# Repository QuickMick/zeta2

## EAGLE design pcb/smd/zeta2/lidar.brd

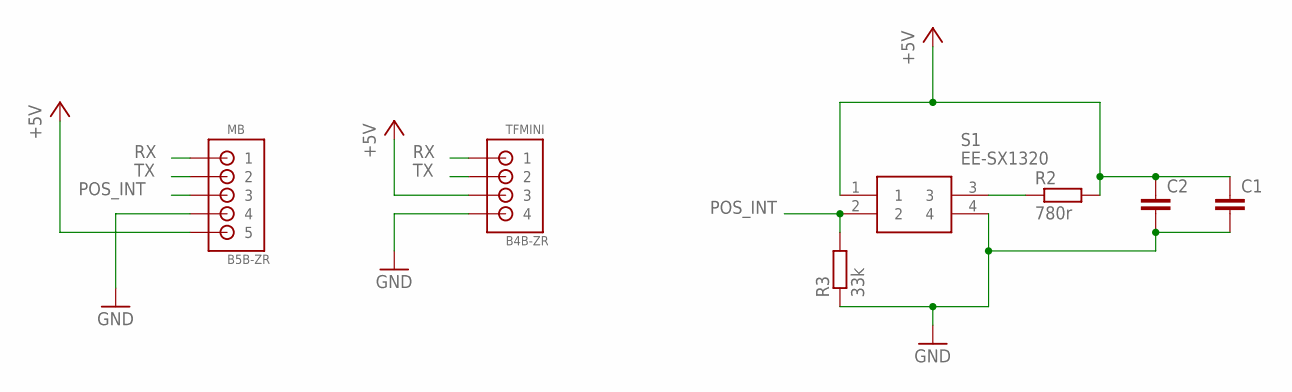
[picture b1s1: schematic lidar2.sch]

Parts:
C1: C-EUC1206; C1206
C2: C-EUC0805; C0805
MB: B5B-ZR
R2: 780r; R0603
R3: 33k; R0603
S1: EE-SX1320
TFMINI: B4B-ZR

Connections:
+5V: C1.1, C2.1, MB.5, R2.2, S1.1, TFMINI.3
GND: C1.2, C2.2, MB.4, R3.1, S1.4, TFMINI.4
unnamed: R2.1, S1.3
POS_INT: MB.3, R3.2, S1.2
RX: MB.1, TFMINI.1
TX: MB.2, TFMINI.2

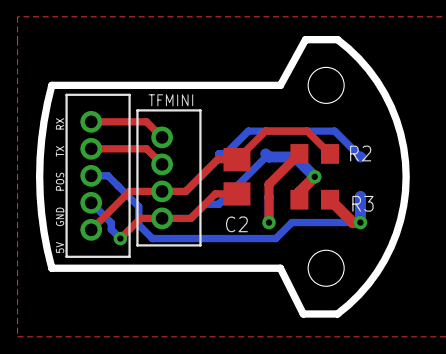
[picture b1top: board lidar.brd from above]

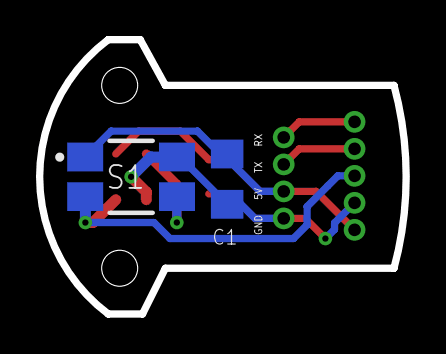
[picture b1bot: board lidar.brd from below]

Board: 2 copper layers, 20.4 x 15.2 mm, 7 parts (2 on the bottom side), 6 nets.

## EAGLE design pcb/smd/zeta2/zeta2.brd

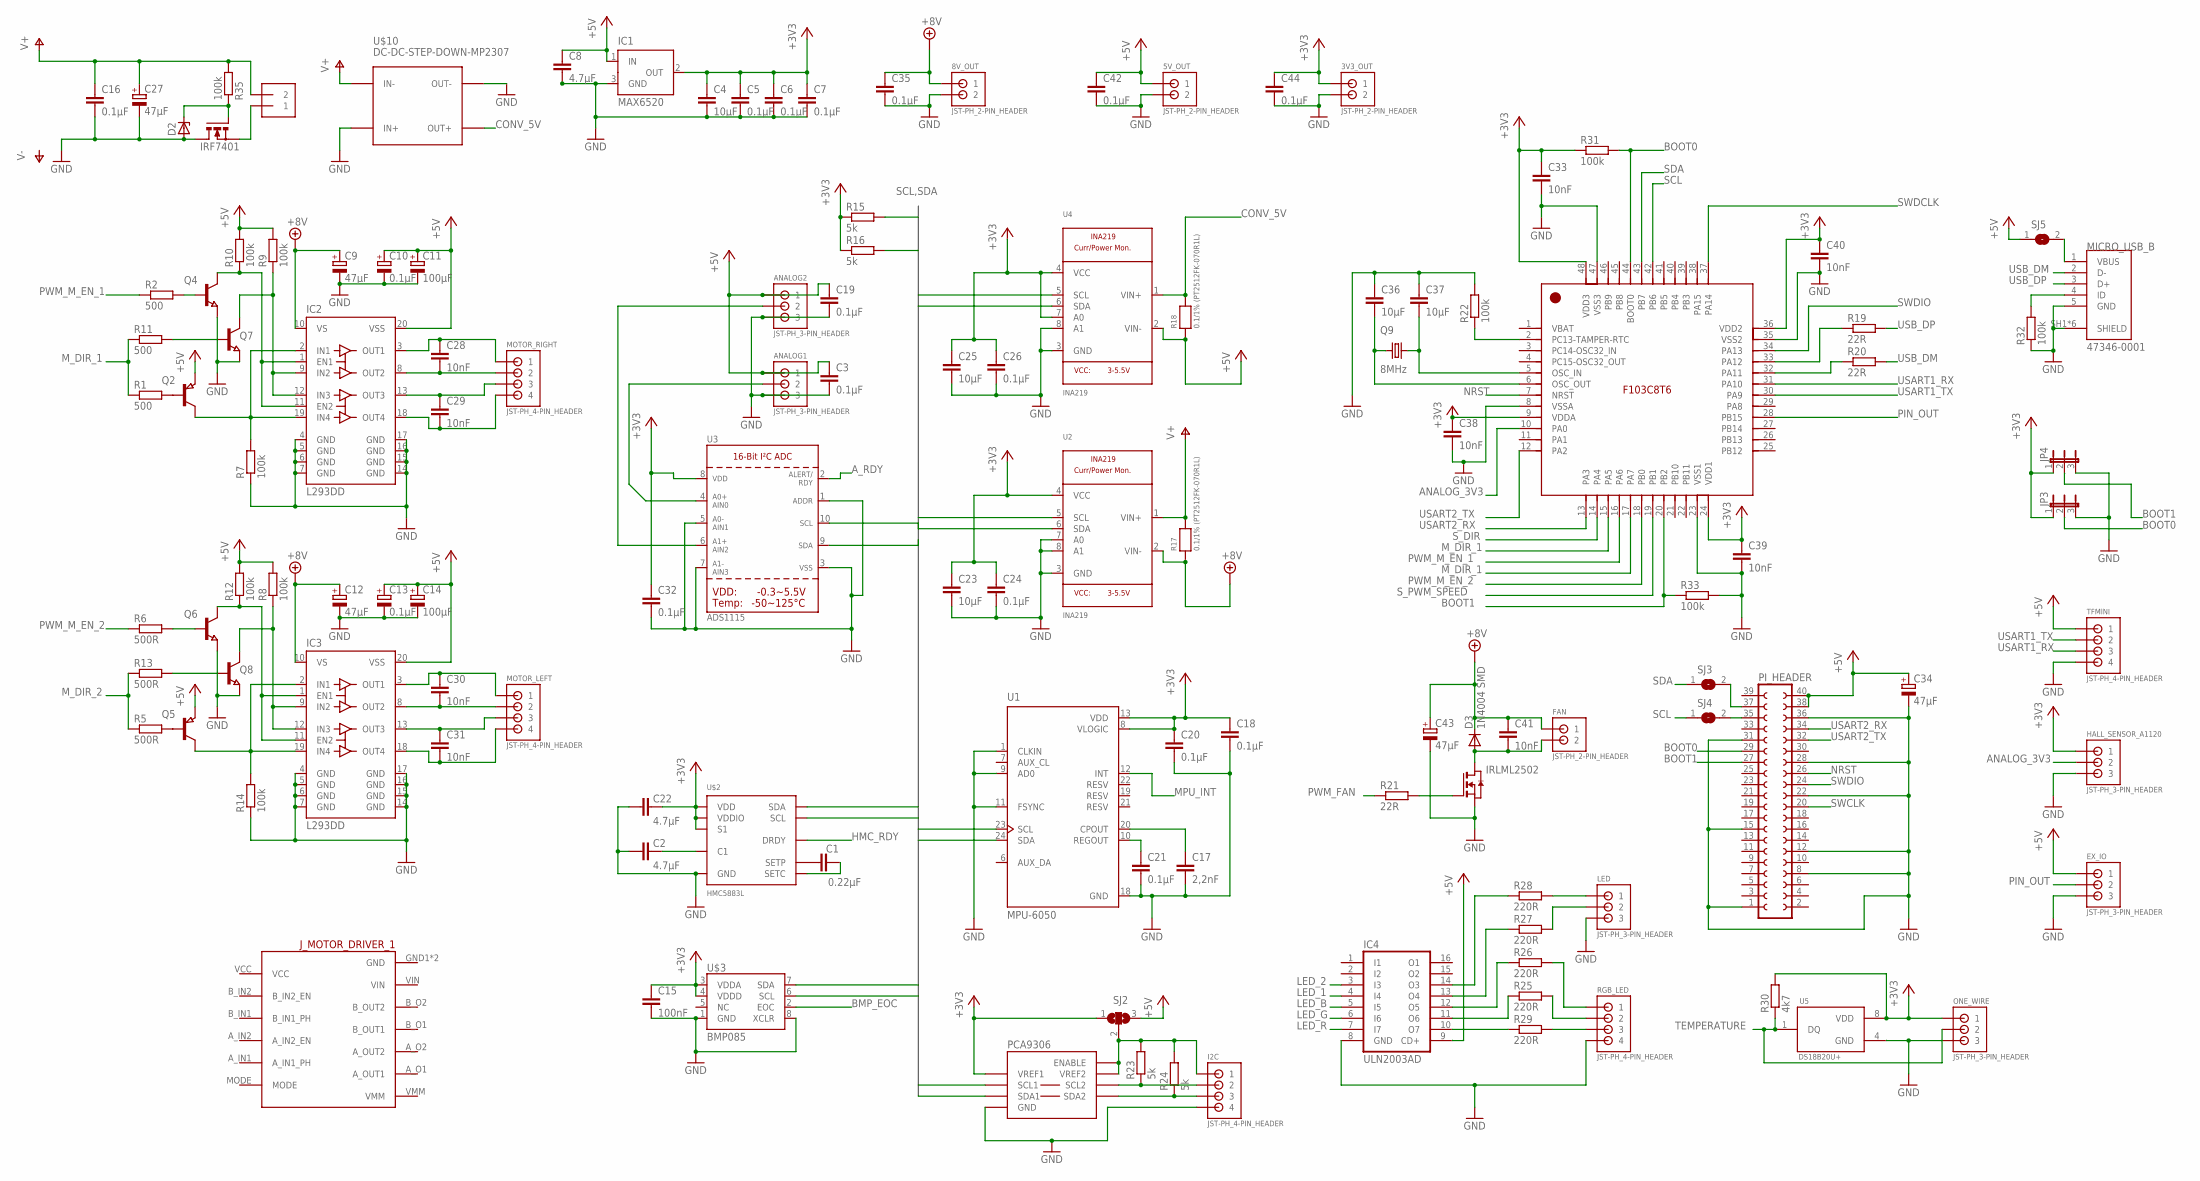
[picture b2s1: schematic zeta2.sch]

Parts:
3V3_OUT, 5V_OUT, 8V_OUT: JST-PH_2-PIN_HEADER; JST_B2B-PH_HEADER
ANALOG1, ANALOG2: JST-PH_3-PIN_HEADER; JST_B3B-PH_HEADER
C1: 0.22µF; C0603
C2, C8, C22: 4.7µF; C0603
C3, C5, C6, C7, C16, C18, C19, C20, C21, C24, C26, C32, C35, C42, C44: 0.1µF; C0603
C4, C23, C25, C36, C37: 10µF; C0603
C9, C12, C27, C34, C43: 47µF; SMC_C
C10, C13: 0.1µF; SMC_A
C11, C14: 100µF; SMC_C
C15: 100nF; C0603
C17: 2,2nF; C0603
C28, C29, C30, C31, C33, C38, C39, C40, C41: 10nF; C0603
D2: ZENER-DIODESOD80C; SOD80C
D3: 1N4004 SMD; MELF-MLL41
EX_IO: JST-PH_3-PIN_HEADER; JST_B3B-PH_HEADER
FAN: JST-PH_2-PIN_HEADER; JST_B2B-PH_HEADER
HALL_SENSOR_A1120: JST-PH_3-PIN_HEADER; JST_B3B-PH_HEADER
I2C: JST-PH_4-PIN_HEADER; JST_B4B-PH_HEADER
IC1: MAX6520; SOT23
IC2, IC3: L293DD; SO20
IC4: ULN2003AD; SO16
IRF7401: N-MOSFET-SO8S; SO-08
IRLML2502: NMOSSOT23; SOT-23
JP3, JP4: JP2E; JP2
J_MOTOR_DRIVER_1: MOTOR_DRIVER; MOTOR_DRIVER_FOOTPRINT
LED: JST-PH_3-PIN_HEADER; JST_B3B-PH_HEADER
MICRO_USB_B: 47346-0001; MOLEX_47346-0001
MOTOR_LEFT: JST-PH_4-PIN_HEADER; JST_B4B-PH_HEADER
MOTOR_RIGHT: JST-PH_4-PIN_HEADER; JST_B4B-PH_HEADER
ONE_WIRE: JST-PH_3-PIN_HEADER; JST_B3B-PH_HEADER
PCA9306: IC2_LEVEL_TRANSLATER; SOIC-8
PI_HEADER: FE20-2
Q2, Q5: PNP-TRANSISTOR_SOT23; SOT23
Q4, Q6, Q7, Q8: NPN-TRANSISTOR_SOT23; SOT23
Q9: 8MHz; 7.0X5.0
R1, R2, R11: 500; R0603
R5, R6, R13: 500R; R0603
R7, R8, R9, R10, R12, R14, R22, R31, R32, R33, R35: 100k; R0603
R15, R16, R23, R24: 5k; R0603
R17, R18: 0.1/1% (PT2512FK-070R1L); 2512
R19, R20, R21: 22R; R0603
R25, R26, R27, R28, R29: 220R; R0603
R30: 4k7; R0603
RGB_LED: JST-PH_4-PIN_HEADER; JST_B4B-PH_HEADER
SJ2: SJ2W; SJ_2
SJ3, SJ4, SJ5: SOLDERJUMPERREFLOW_NOPASTE; SOLDERJUMPER_REFLOW_NOPASTE
SUPPLY_IN: TERMBLOCK_1X2-3.5MM; 1X2-3.5MM
TFMINI: JST-PH_4-PIN_HEADER; JST_B4B-PH_HEADER
U1: MPU-6050; QFN50P400X400X95-24N
U2, U4: INA219; SOT23-8
U3: ADS1115; MSOP10
U5: DS18B20U+; SOP65P490X95-8N
U$1: STM32F103C8T6; LQFP48_7X7MM_0.5MMPP
U$2: HMC5883L; LPCC-16
U$3: BMP085
U$10: DC-DC-STEP-DOWN-MP2307

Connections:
+3V3: 3V3_OUT.P1 (1), C4.1, C5.1, C6.1, C7.1, C15.1, C18.1, C20.1, C22.1, C23.1, C24.1, C25.1, C26.1, C32.1, C33.1, C38.1, C39.1, C40.1, C44.1, HALL_SENSOR_A1120.P1 (1), IC1.2 (OUT), JP3.1, JP4.1, ONE_WIRE.P1 (1), PCA9306.1 (VREF1), R15.1, R16.1, R30.2, R31.1, SJ2.1, U1.8 (VLOGIC), U1.13 (VDD), U2.4 (VCC), U3.8 (VDD), U4.4 (VCC), U4.7 (A0), U5.8 (VDD), U$1.9 (VDDA), U$1.24 (VDD1), U$1.36 (VDD2), U$1.48 (VDD3), U$2.2 (VDD), U$2.4 (S1), U$2.13 (VDDIO), U$3.3 (VDDA), U$3.4 (VDDD)
+5V: 5V_OUT.P1 (1), ANALOG1.P1 (1), ANALOG2.P1 (1), C3.1, C8.1, C10.+, C11.+, C13.+, C14.+, C19.1, C34.+, C42.1, EX_IO.P1 (1), IC1.1 (IN), IC2.20 (VSS), IC3.20 (VSS), IC4.9 (CD+), PI_HEADER.38, PI_HEADER.40, Q2.2 (E), Q5.2 (E), R8.2, R9.2, R10.2, R12.2, R18.1, SJ2.3, SJ5.1, TFMINI.P1 (1), U4.2 (VIN-)
+8V: 8V_OUT.P1 (1), C9.+, C12.+, C35.1, C41.1, C43.+, D3.C, FAN.P1 (1), IC2.10 (VS), IC3.10 (VS), R17.1, U2.2 (VIN-)
ANALOG_3V3: HALL_SENSOR_A1120.P2 (2), U$1.10 (PA0)
A_RDY: U3.2 (ALERT/RDY)
BMP_EOC: U$3.2 (EOC)
BOOT0: JP3.2, PI_HEADER.29, R31.2, U$1.44 (BOOT0)
BOOT1: JP4.2, PI_HEADER.27, R33.1, U$1.20 (PB2)
CONV_5V: R18.2, U4.1 (VIN+), U$10.OUT+
GND: 3V3_OUT.P2 (2), 5V_OUT.P2 (2), 8V_OUT.P2 (2), ANALOG1.P3 (3), ANALOG2.P3 (3), C2.2, C3.2, C4.2, C5.2, C6.2, C7.2, C8.2, C9.-, C10.-, C11.-, C12.-, C13.-, C14.-, C15.2, C16.2, C17.2, C18.2, C19.2, C20.2, C21.2, C22.2, C23.2, C24.2, C25.2, C26.2, C27.-, C32.2, C33.2, C34.-, C35.2, C36.1, C37.1, C38.2, C39.2, C40.2, C42.2, C43.-, C44.2, D2.A, EX_IO.P3 (3), HALL_SENSOR_A1120.P3 (3), I2C.P4 (4), IC1.3 (GND), IC2.4 (GND), IC2.5 (GND), IC2.6 (GND), IC2.7 (GND), IC2.14 (GND), IC2.15 (GND), IC2.16 (GND), IC2.17 (GND), IC3.4 (GND), IC3.5 (GND), IC3.6 (GND), IC3.7 (GND), IC3.14 (GND), IC3.15 (GND), IC3.16 (GND), IC3.17 (GND), IC4.8 (GND), IRF7401.5 (D), IRF7401.6 (D), IRF7401.7 (D), IRF7401.8 (D), IRLML2502.2 (S), JP3.3, JP4.3, LED.P3 (3), MICRO_USB_B.5 (GND), MICRO_USB_B.SH1 (SHIELD), MICRO_USB_B.SH2 (SHIELD), MICRO_USB_B.SH3 (SHIELD), MICRO_USB_B.SH4 (SHIELD), MICRO_USB_B.SH5 (SHIELD), MICRO_USB_B.SH6 (SHIELD), ONE_WIRE.P3 (3), PCA9306.4 (GND), PI_HEADER.1, PI_HEADER.8, PI_HEADER.12, PI_HEADER.15, PI_HEADER.22, PI_HEADER.28, PI_HEADER.31, PI_HEADER.36, Q4.2 (E), Q6.2 (E), Q7.2 (E), Q8.2 (E), R7.1, R14.1, R22.2, R32.1, R33.2, RGB_LED.P4 (4), TFMINI.P4 (4), U1.1 (CLKIN), U1.9 (AD0), U1.11 (FSYNC), U1.18 (GND), U2.3 (GND), U2.7 (A0), U2.8 (A1), U3.1 (ADDR), U3.3 (VSS), U3.5 (AIN1), U3.7 (AIN3), U4.3 (GND), U4.8 (A1), U5.4 (GND), U$1.8 (VSSA), U$1.23 (VSS1), U$1.35 (VSS2), U$1.47 (VSS3), U$2.9 (GND), U$2.11 (GND), U$3.1 (GND), U$3.8 (XCLR), U$10.IN+, U$10.OUT-
HMC_RDY: U$2.15 (DRDY)
LED_1: IC4.4 (I4)
LED_2: IC4.3 (I3)
LED_B: IC4.5 (I5)
LED_G: IC4.6 (I6)
LED_R: IC4.7 (I7)
MPU_INT: U1.12 (INT)
M_DIR_1: R1.1, R11.1, U$1.15 (PA5), U$1.17 (PA7)
M_DIR_2: R5.1, R13.1
unnamed: IC2.9 (IN2), IC2.12 (IN3), Q7.3 (C), R9.1
unnamed: C1.2, U$2.12 (SETC)
unnamed: C1.1, U$2.8 (SETP)
unnamed: C2.1, U$2.10 (C1)
unnamed: IC2.2 (IN1), IC2.19 (IN4), Q2.3 (C), R7.2
unnamed: IC3.9 (IN2), IC3.12 (IN3), Q8.3 (C), R8.1
unnamed: IC3.2 (IN1), IC3.19 (IN4), Q5.3 (C), R14.2
unnamed: IC2.1 (EN1), IC2.11 (EN2), Q4.3 (C), R10.1
unnamed: IC3.1 (EN1), IC3.11 (EN2), Q6.3 (C), R12.1
unnamed: Q2.1 (B), R1.2
unnamed: Q7.1 (B), R11.2
unnamed: Q4.1 (B), R2.2
unnamed: Q5.1 (B), R5.2
unnamed: Q6.1 (B), R6.2
unnamed: Q8.1 (B), R13.2
unnamed: C17.1, U1.20 (CPOUT)
unnamed: C29.1, IC2.13 (OUT3), MOTOR_RIGHT.P3 (3)
unnamed: C29.2, IC2.18 (OUT4), MOTOR_RIGHT.P4 (4)
unnamed: C21.1, U1.10 (REGOUT)
unnamed: C28.2, IC2.8 (OUT2), MOTOR_RIGHT.P2 (2)
unnamed: C28.1, IC2.3 (OUT1), MOTOR_RIGHT.P1 (1)
unnamed: C31.1, IC3.13 (OUT3), MOTOR_LEFT.P3 (3)
unnamed: C31.2, IC3.18 (OUT4), MOTOR_LEFT.P4 (4)
unnamed: C30.2, IC3.8 (OUT2), MOTOR_LEFT.P2 (2)
unnamed: C30.1, IC3.3 (OUT1), MOTOR_LEFT.P1 (1)
unnamed: IC4.10 (O7), R29.1
unnamed: C36.2, Q9.1, U$1.6 (OSC_OUT)
unnamed: C37.2, Q9.3 (2), U$1.5 (OSC_IN)
unnamed: IRLML2502.3 (G), R21.2
unnamed: IC4.11 (O6), R25.1
unnamed: R20.1, U$1.32 (PA11)
unnamed: R19.1, U$1.33 (PA12)
unnamed: R22.1, U$1.2 (PC13-TAMPER-RTC)
unnamed: PI_HEADER.37, SJ3.2
unnamed: PI_HEADER.35, SJ4.2
unnamed: IC4.12 (O5), R26.1
unnamed: I2C.P1 (1), PCA9306.7 (VREF2), PCA9306.8 (ENABLE), R23.2, R24.2, SJ2.2
unnamed: I2C.P2 (2), PCA9306.6 (SCL2), R23.1
unnamed: I2C.P3 (3), PCA9306.5 (SDA2), R24.1
unnamed: IC4.13 (O4), R27.1
unnamed: IC4.14 (O3), R28.1
unnamed: MICRO_USB_B.4 (ID), R32.2
unnamed: LED.P1 (1), R28.2
unnamed: R29.2, RGB_LED.P3 (3)
unnamed: R25.2, RGB_LED.P2 (2)
unnamed: R26.2, RGB_LED.P1 (1)
unnamed: LED.P2 (2), R27.2
unnamed: MICRO_USB_B.1 (VBUS), SJ5.2
unnamed: ANALOG1.P2 (2), U3.4 (AIN0)
unnamed: ANALOG2.P2 (2), U3.6 (AIN2)
unnamed: C41.2, D3.A, FAN.P2 (2), IRLML2502.1 (D)
unnamed: D2.C, IRF7401.4 (G), R35.1
unnamed: IRF7401.1 (S), IRF7401.2 (S), IRF7401.3 (S), SUPPLY_IN.1
NRST: PI_HEADER.26, U$1.7 (NRST)
PIN_OUT: EX_IO.P2 (2), U$1.28 (PB15)
PWM_FAN: R21.1
PWM_M_EN_1: R2.1, U$1.16 (PA6)
PWM_M_EN_2: R6.1, U$1.18 (PB0)
SCL: PCA9306.2 (SCL1), R15.2, SJ4.1, U1.23 (SCL), U2.5 (SCL), U3.10 (SCL), U4.5 (SCL), U$1.42 (PB6), U$2.1 (SCL), U$3.6 (SCL)
SDA: PCA9306.3 (SDA1), R16.2, SJ3.1, U1.24 (SDA), U2.6 (SDA), U3.9 (SDA), U4.6 (SDA), U$1.43 (PB7), U$2.16 (SDA), U$3.7 (SDA)
SWCLK: PI_HEADER.20
SWDCLK: U$1.37 (PA14)
SWDIO: PI_HEADER.24, U$1.34 (PA13)
S_DIR: U$1.14 (PA4)
S_PWM_SPEED: U$1.19 (PB1)
TEMPERATURE: ONE_WIRE.P2 (2), R30.1, U5.1 (DQ)
USART1_RX: TFMINI.P3 (3), U$1.31 (PA10)
USART1_TX: TFMINI.P2 (2), U$1.30 (PA9)
USART2_RX: PI_HEADER.34, U$1.13 (PA3)
USART2_TX: PI_HEADER.32, U$1.12 (PA2)
USB_DM: MICRO_USB_B.2 (D-), R20.2
USB_DP: MICRO_USB_B.3 (D+), R19.2
V+: C16.1, C27.+, R17.2, R35.2, SUPPLY_IN.2, U2.1 (VIN+), U$10.IN-

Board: 2 copper layers, 126 parts (16 on the bottom side), 78 nets, no tracks yet.

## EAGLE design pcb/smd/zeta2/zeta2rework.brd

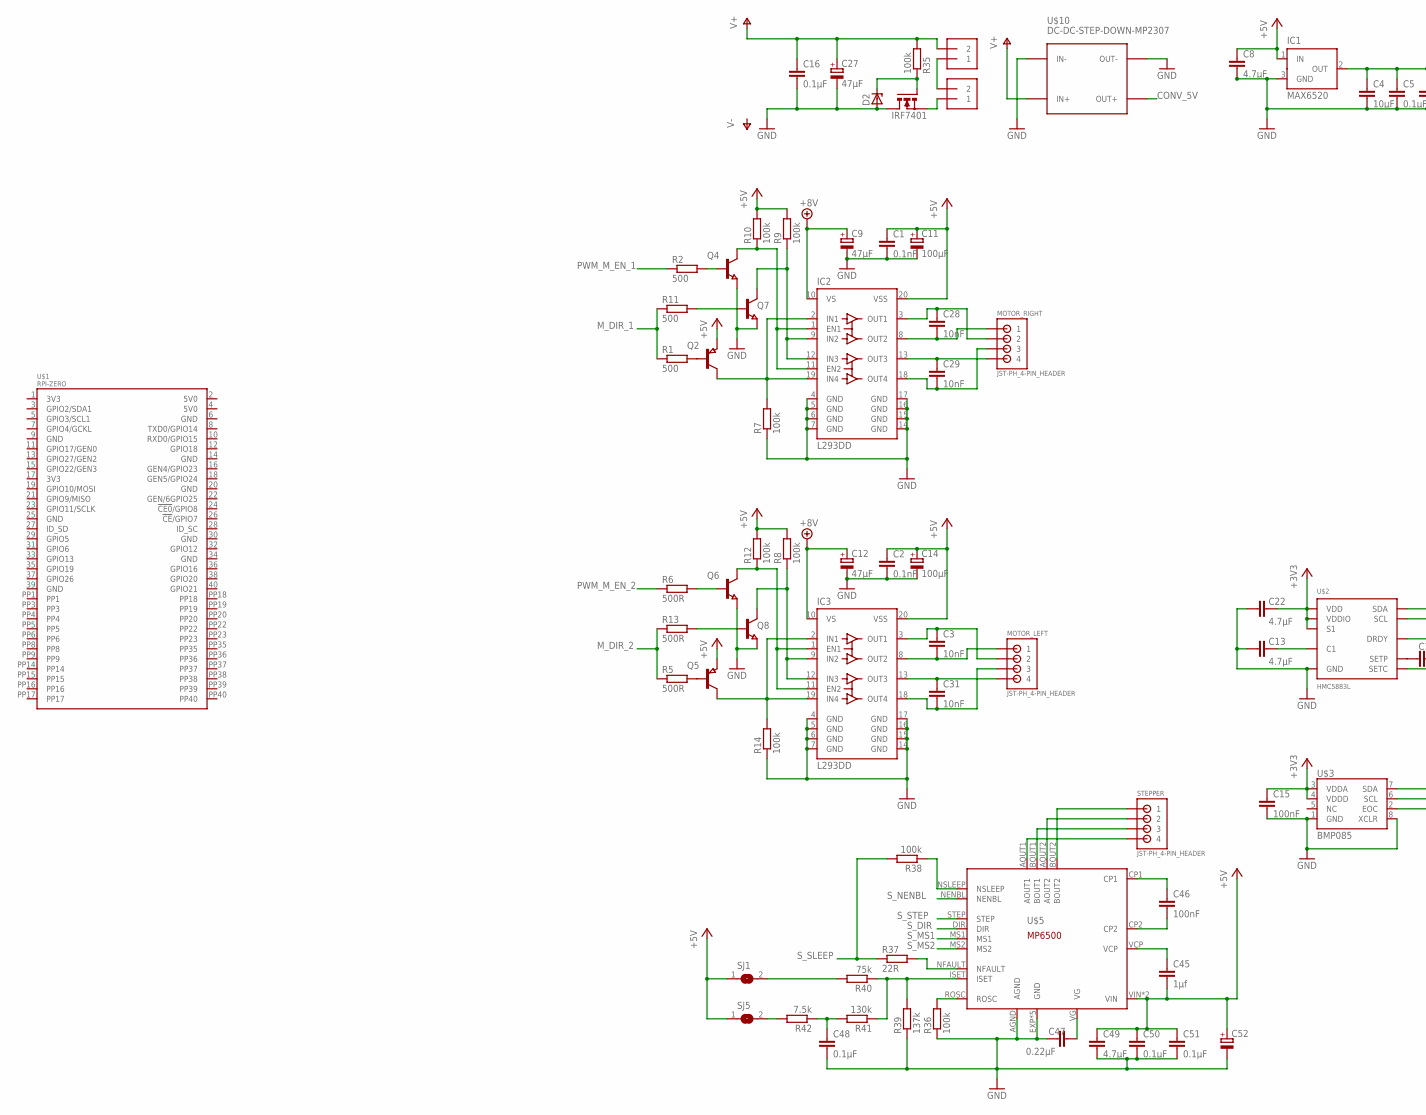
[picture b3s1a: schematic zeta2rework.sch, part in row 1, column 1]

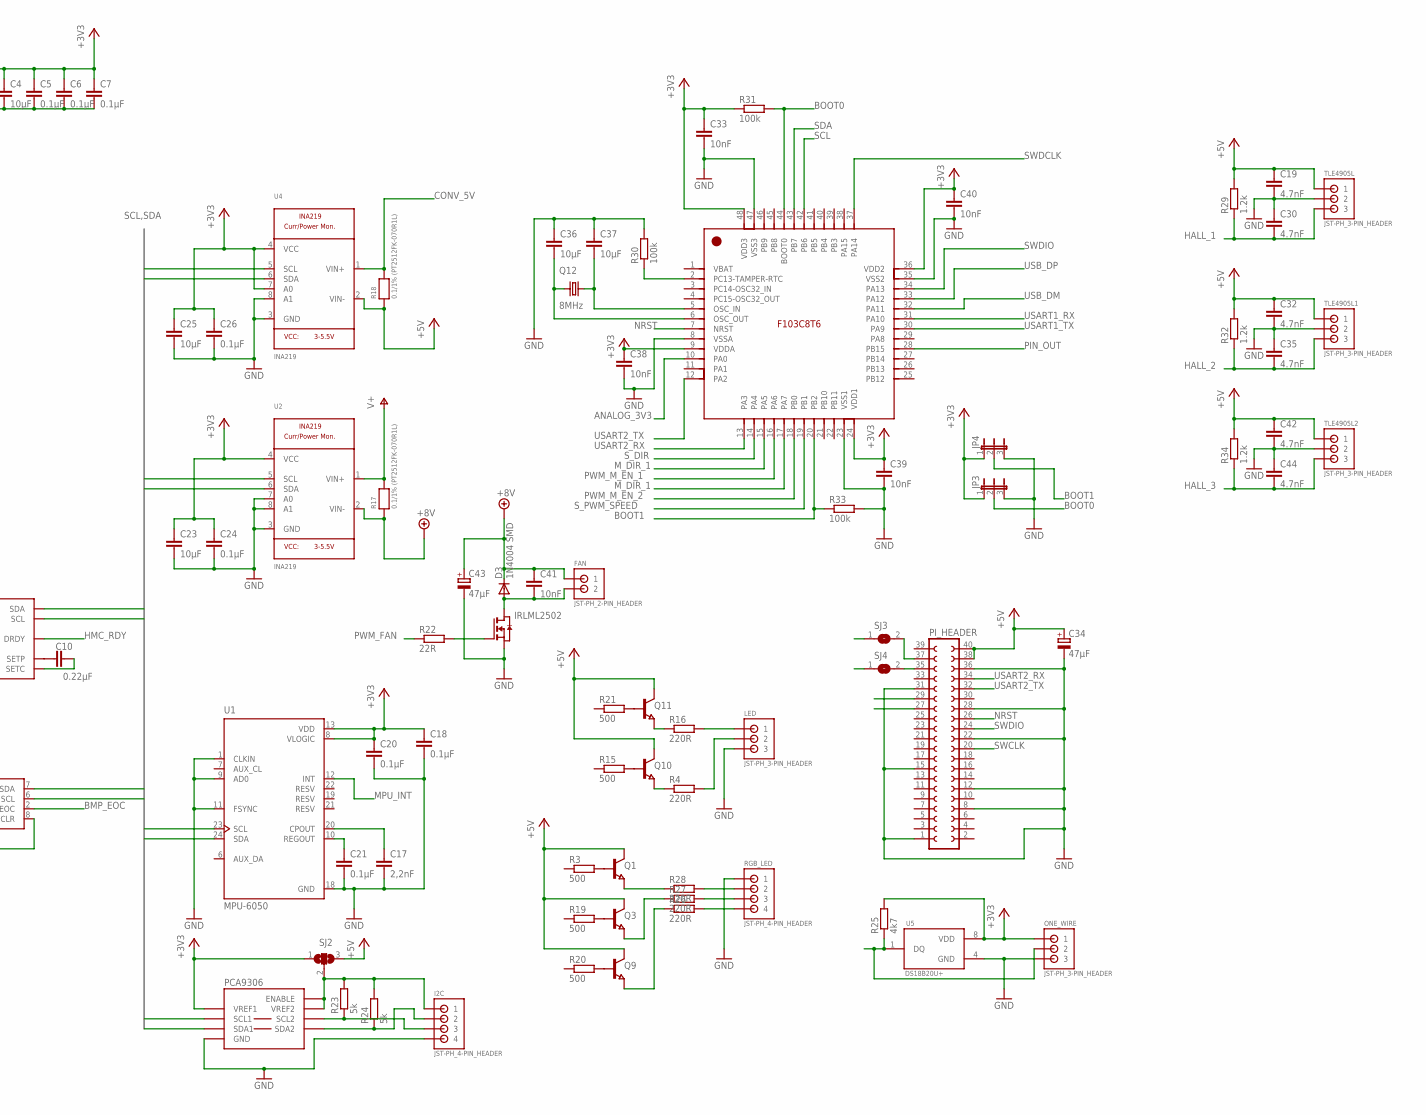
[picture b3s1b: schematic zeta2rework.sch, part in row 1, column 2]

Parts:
C1, C2: 0.1nF; C0603
C3, C28, C29, C31, C33, C38, C39, C40, C41: 10nF; C0603
C4, C23, C25, C36, C37: 10µF; C0603
C5, C6, C7, C16, C18, C20, C21, C24, C26, C48, C50, C51: 0.1µF; C0603
C8, C13, C22, C49: 4.7µF; C0603
C9, C12, C27, C34, C43: 47µF; SMC_C
C10, C47: 0.22µF; C0603
C11, C14: 100µF; SMC_C
C15, C46: 100nF; C0603
C17: 2,2nF; C0603
C19, C30, C32, C35, C42, C44: 4.7nF; C0603
C45: 1µf; C0603
C52: CPOL-EU150CLZ-0810; 150CLZ-0810
D2: ZENER-DIODESOD80C; SOD80C
D3: 1N4004 SMD; MELF-MLL41
FAN: JST-PH_2-PIN_HEADER; JST_B2B-PH_HEADER
I2C: JST-PH_4-PIN_HEADER; JST_B4B-PH_HEADER
IC1: MAX6520; SOT23
IC2, IC3: L293DD; SO20
IRF7401: N-MOSFET-SO8S; SO-08
IRLML2502: NMOSSOT23; SOT-23
JP3, JP4: JP2E; JP2
LED: JST-PH_3-PIN_HEADER; JST_B3B-PH_HEADER
MOTOR_LEFT: JST-PH_4-PIN_HEADER; JST_B4B-PH_HEADER
MOTOR_RIGHT: JST-PH_4-PIN_HEADER; JST_B4B-PH_HEADER
ONE_WIRE: JST-PH_3-PIN_HEADER; JST_B3B-PH_HEADER
PCA9306: IC2_LEVEL_TRANSLATER; SOIC-8
PI_HEADER: FE20-2
Q1, Q3, Q4, Q6, Q7, Q8, Q9, Q10, Q11: NPN-TRANSISTOR_SOT23; SOT23
Q2, Q5: PNP-TRANSISTOR_SOT23; SOT23
Q12: 8MHz; 7.0X5.0
R1, R2, R3, R11, R15, R19, R20, R21: 500; R0603
R4, R16, R26, R27, R28: 220R; R0603
R5, R6, R13: 500R; R0603
R7, R8, R9, R10, R12, R14, R30, R31, R33, R35, R36, R38: 100k; R0603
R17, R18: 0.1/1% (PT2512FK-070R1L); 2512
R22, R37: 22R; R0603
R23, R24: 5k; R0603
R25: 4k7; R0603
R29, R32, R34: 1.2k; R0603
R39: 137k; R0603
R40: 75k; R0603
R41: 130k; R0603
R42: 7.5k; R0603
RGB_LED: JST-PH_4-PIN_HEADER; JST_B4B-PH_HEADER
SJ1, SJ3, SJ4, SJ5: SOLDERJUMPERREFLOW_NOPASTE; SOLDERJUMPER_REFLOW_NOPASTE
SJ2: SJ2W; SJ_2
STEPPER: JST-PH_4-PIN_HEADER; JST_B4B-PH_HEADER
SUPPLY_IN, SUPPLY_IN1: TERMBLOCK_1X2-3.5MM; 1X2-3.5MM
TLE4905L, TLE4905L1, TLE4905L2: JST-PH_3-PIN_HEADER; JST_B3B-PH_HEADER
U1: MPU-6050; QFN50P400X400X95-24N
U2, U4: INA219; SOT23-8
U5: DS18B20U+; SOP65P490X95-8N
U$1: RPI-ZERO; RASP_PI_ZERO_BOARD_FULL
U$2: HMC5883L; LPCC-16
U$3: BMP085
U$4: STM32F103C8T6; LQFP48_7X7MM_0.5MMPP
U$5: MP6500; QFN24
U$10: DC-DC-STEP-DOWN-MP2307

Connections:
+3V3: C4.1, C5.1, C6.1, C7.1, C15.1, C18.1, C20.1, C22.1, C23.1, C24.1, C25.1, C26.1, C33.1, C38.1, C39.1, C40.1, IC1.2 (OUT), JP3.1, JP4.1, ONE_WIRE.P1 (1), PCA9306.1 (VREF1), R25.2, R31.1, SJ2.1, U1.8 (VLOGIC), U1.13 (VDD), U2.4 (VCC), U4.4 (VCC), U4.7 (A0), U5.8 (VDD), U$2.2 (VDD), U$2.4 (S1), U$2.13 (VDDIO), U$3.3 (VDDA), U$3.4 (VDDD), U$4.9 (VDDA), U$4.24 (VDD1), U$4.36 (VDD2), U$4.48 (VDD3)
+5V: C1.1, C2.1, C8.1, C11.+, C14.+, C19.1, C32.1, C34.+, C42.1, C45.2, C49.1, C50.1, C51.1, C52.+, IC1.1 (IN), IC2.20 (VSS), IC3.20 (VSS), PI_HEADER.38, PI_HEADER.40, Q1.3 (C), Q2.2 (E), Q3.3 (C), Q5.2 (E), Q9.3 (C), Q10.3 (C), Q11.3 (C), R8.2, R9.2, R10.2, R12.2, R18.1, R29.2, R32.2, R34.2, SJ1.1, SJ2.3, SJ5.1, TLE4905L.P1 (1), TLE4905L1.P1 (1), TLE4905L2.P1 (1), U4.2 (VIN-), U$5.VIN, U$5.VIN@1 (VIN)
+8V: C9.+, C12.+, C41.1, C43.+, D3.C, FAN.P1 (1), IC2.10 (VS), IC3.10 (VS), R17.1, U2.2 (VIN-)
ANALOG_3V3: U$4.10 (PA0)
BMP_EOC: U$3.2 (EOC)
BOOT0: JP3.2, R31.2, U$4.44 (BOOT0)
BOOT1: JP4.2, R33.1, U$4.20 (PB2)
BOOT2: PI_HEADER.29
BOOT3: PI_HEADER.27
CONV_5V: R18.2, U4.1 (VIN+), U$10.OUT+
GND: C1.2, C2.2, C4.2, C5.2, C6.2, C7.2, C8.2, C9.-, C11.-, C12.-, C13.2, C14.-, C15.2, C16.2, C17.2, C18.2, C19.2, C20.2, C21.2, C22.2, C23.2, C24.2, C25.2, C26.2, C27.-, C30.1, C32.2, C33.2, C34.-, C35.1, C36.1, C37.1, C38.2, C39.2, C40.2, C42.2, C43.-, C44.1, C47.1, C48.2, C49.2, C50.2, C51.2, C52.-, D2.A, I2C.P4 (4), IC1.3 (GND), IC2.4 (GND), IC2.5 (GND), IC2.6 (GND), IC2.7 (GND), IC2.14 (GND), IC2.15 (GND), IC2.16 (GND), IC2.17 (GND), IC3.4 (GND), IC3.5 (GND), IC3.6 (GND), IC3.7 (GND), IC3.14 (GND), IC3.15 (GND), IC3.16 (GND), IC3.17 (GND), IRF7401.5 (D), IRF7401.6 (D), IRF7401.7 (D), IRF7401.8 (D), IRLML2502.2 (S), JP3.3, JP4.3, LED.P3 (3), ONE_WIRE.P3 (3), PCA9306.4 (GND), PI_HEADER.1, PI_HEADER.8, PI_HEADER.12, PI_HEADER.15, PI_HEADER.22, PI_HEADER.28, PI_HEADER.31, PI_HEADER.36, Q4.2 (E), Q6.2 (E), Q7.2 (E), Q8.2 (E), R7.1, R14.1, R30.2, R33.2, R36.1, R39.1, RGB_LED.P1 (1), TLE4905L.P2 (2), TLE4905L1.P2 (2), TLE4905L2.P2 (2), U1.1 (CLKIN), U1.9 (AD0), U1.11 (FSYNC), U1.18 (GND), U2.3 (GND), U2.7 (A0), U2.8 (A1), U4.3 (GND), U4.8 (A1), U5.4 (GND), U$2.9 (GND), U$2.11 (GND), U$3.1 (GND), U$3.8 (XCLR), U$4.8 (VSSA), U$4.23 (VSS1), U$4.35 (VSS2), U$4.47 (VSS3), U$5.AGND, U$5.EXP (GND), U$5.GND@1 (GND), U$5.GND@2 (GND), U$5.GND@3 (GND), U$5.GND@4 (GND), U$10.IN-, U$10.OUT-
HALL_1: C30.2, R29.1, TLE4905L.P3 (3)
HALL_2: C35.2, R32.1, TLE4905L1.P3 (3)
HALL_3: C44.2, R34.1, TLE4905L2.P3 (3)
HMC_RDY: U$2.15 (DRDY)
MPU_INT: U1.12 (INT)
M_DIR_1: R1.1, R11.1, U$4.15 (PA5), U$4.17 (PA7)
M_DIR_2: R5.1, R13.1
unnamed: IC2.9 (IN2), IC2.12 (IN3), Q7.3 (C), R9.1
unnamed: C31.2, IC3.18 (OUT4), MOTOR_LEFT.P3 (3)
unnamed: C31.1, IC3.13 (OUT3), MOTOR_LEFT.P4 (4)
unnamed: R26.2, RGB_LED.P4 (4)
unnamed: IC2.2 (IN1), IC2.19 (IN4), Q2.3 (C), R7.2
unnamed: IC3.9 (IN2), IC3.12 (IN3), Q8.3 (C), R8.1
unnamed: IC3.2 (IN1), IC3.19 (IN4), Q5.3 (C), R14.2
unnamed: IC2.1 (EN1), IC2.11 (EN2), Q4.3 (C), R10.1
unnamed: IC3.1 (EN1), IC3.11 (EN2), Q6.3 (C), R12.1
unnamed: Q2.1 (B), R1.2
unnamed: Q7.1 (B), R11.2
unnamed: Q4.1 (B), R2.2
unnamed: Q5.1 (B), R5.2
unnamed: Q6.1 (B), R6.2
unnamed: Q8.1 (B), R13.2
unnamed: R27.2, RGB_LED.P3 (3)
unnamed: C29.1, IC2.13 (OUT3), MOTOR_RIGHT.P4 (4)
unnamed: C29.2, IC2.18 (OUT4), MOTOR_RIGHT.P3 (3)
unnamed: R28.2, RGB_LED.P2 (2)
unnamed: C28.2, IC2.8 (OUT2), MOTOR_RIGHT.P1 (1)
unnamed: C28.1, IC2.3 (OUT1), MOTOR_RIGHT.P2 (2)
unnamed: Q1.1 (B), R3.2
unnamed: Q3.1 (B), R19.2
unnamed: Q1.2 (E), R28.1
unnamed: C3.2, IC3.8 (OUT2), MOTOR_LEFT.P1 (1)
unnamed: C3.1, IC3.3 (OUT1), MOTOR_LEFT.P2 (2)
unnamed: Q10.1 (B), R15.2
unnamed: Q3.2 (E), R27.1
unnamed: Q9.2 (E), R26.1
unnamed: Q10.2 (E), R4.1
unnamed: Q11.1 (B), R21.2
unnamed: Q9.1 (B), R20.2
unnamed: Q11.2 (E), R16.1
unnamed: C17.1, U1.20 (CPOUT)
unnamed: LED.P1 (1), R16.2
unnamed: C21.1, U1.10 (REGOUT)
unnamed: IRLML2502.3 (G), R22.2
unnamed: C10.2, U$2.12 (SETC)
unnamed: C10.1, U$2.8 (SETP)
unnamed: C13.1, U$2.10 (C1)
unnamed: I2C.P1 (1), PCA9306.7 (VREF2), PCA9306.8 (ENABLE), R23.2, R24.2, SJ2.2
unnamed: I2C.P3 (3), PCA9306.6 (SCL2), R23.1
unnamed: I2C.P2 (2), PCA9306.5 (SDA2), R24.1
unnamed: PI_HEADER.37, SJ3.2
unnamed: PI_HEADER.35, SJ4.2
unnamed: C36.2, Q12.1, U$4.6 (OSC_OUT)
unnamed: C37.2, Q12.3 (2), U$4.5 (OSC_IN)
unnamed: LED.P2 (2), R4.2
unnamed: R30.1, U$4.2 (PC13-TAMPER-RTC)
unnamed: SUPPLY_IN.1, SUPPLY_IN1.2
unnamed: C45.1, U$5.VCP
unnamed: R38.1, U$5.NSLEEP
unnamed: C46.2, U$5.CP2
unnamed: C46.1, U$5.CP1
unnamed: C41.2, D3.A, FAN.P2 (2), IRLML2502.1 (D)
unnamed: D2.C, IRF7401.4 (G), R35.1
unnamed: C47.2, U$5.VG
unnamed: R36.2, U$5.ROSC
unnamed: R37.2, U$5.NFAULT
unnamed: IRF7401.1 (S), IRF7401.2 (S), IRF7401.3 (S), SUPPLY_IN1.1
unnamed: STEPPER.P1 (1), U$5.BOUT2
unnamed: STEPPER.P2 (2), U$5.AOUT2
unnamed: R39.2, R40.1, R41.1, U$5.ISET
unnamed: STEPPER.P3 (3), U$5.BOUT1
unnamed: R40.2, SJ1.2
unnamed: R42.2, SJ5.2
unnamed: C48.1, R41.2, R42.1
unnamed: STEPPER.P4 (4), U$5.AOUT1
NRST: PI_HEADER.26, U$4.7 (NRST)
PIN_OUT: U$4.28 (PB15)
PWM_FAN: R22.1
PWM_M_EN_1: R2.1, U$4.16 (PA6)
PWM_M_EN_2: R6.1, U$4.18 (PB0)
SCL: U1.23 (SCL), U2.5 (SCL), U4.5 (SCL), U$3.6 (SCL), U$4.42 (PB6)
SCL1: U$2.1 (SCL)
SCL2: PCA9306.2 (SCL1)
SCL3: SJ4.1
SDA: U1.24 (SDA), U2.6 (SDA), U4.6 (SDA), U$3.7 (SDA), U$4.43 (PB7)
SDA1: U$2.16 (SDA)
SDA2: PCA9306.3 (SDA1)
SDA3: SJ3.1
SWCLK: PI_HEADER.20
SWDCLK: U$4.37 (PA14)
SWDIO: PI_HEADER.24, U$4.34 (PA13)
S_DIR: U$4.14 (PA4), U$5.DIR
S_MS1: U$5.MS1
S_MS2: U$5.MS2
S_NENBL: U$5.NENBL
S_PWM_SPEED: U$4.19 (PB1)
S_SLEEP: R37.1, R38.2
S_STEP: U$5.STEP
TEMPERATURE: ONE_WIRE.P2 (2), R25.1, U5.1 (DQ)
USART1_RX: U$4.31 (PA10)
USART1_TX: U$4.30 (PA9)
USART2_RX: PI_HEADER.34, U$4.13 (PA3)
USART2_TX: PI_HEADER.32, U$4.12 (PA2)
USB_DM: U$4.32 (PA11)
USB_DP: U$4.33 (PA12)
V+: C16.1, C27.+, R17.2, R35.2, SUPPLY_IN.2, U2.1 (VIN+), U$10.IN+

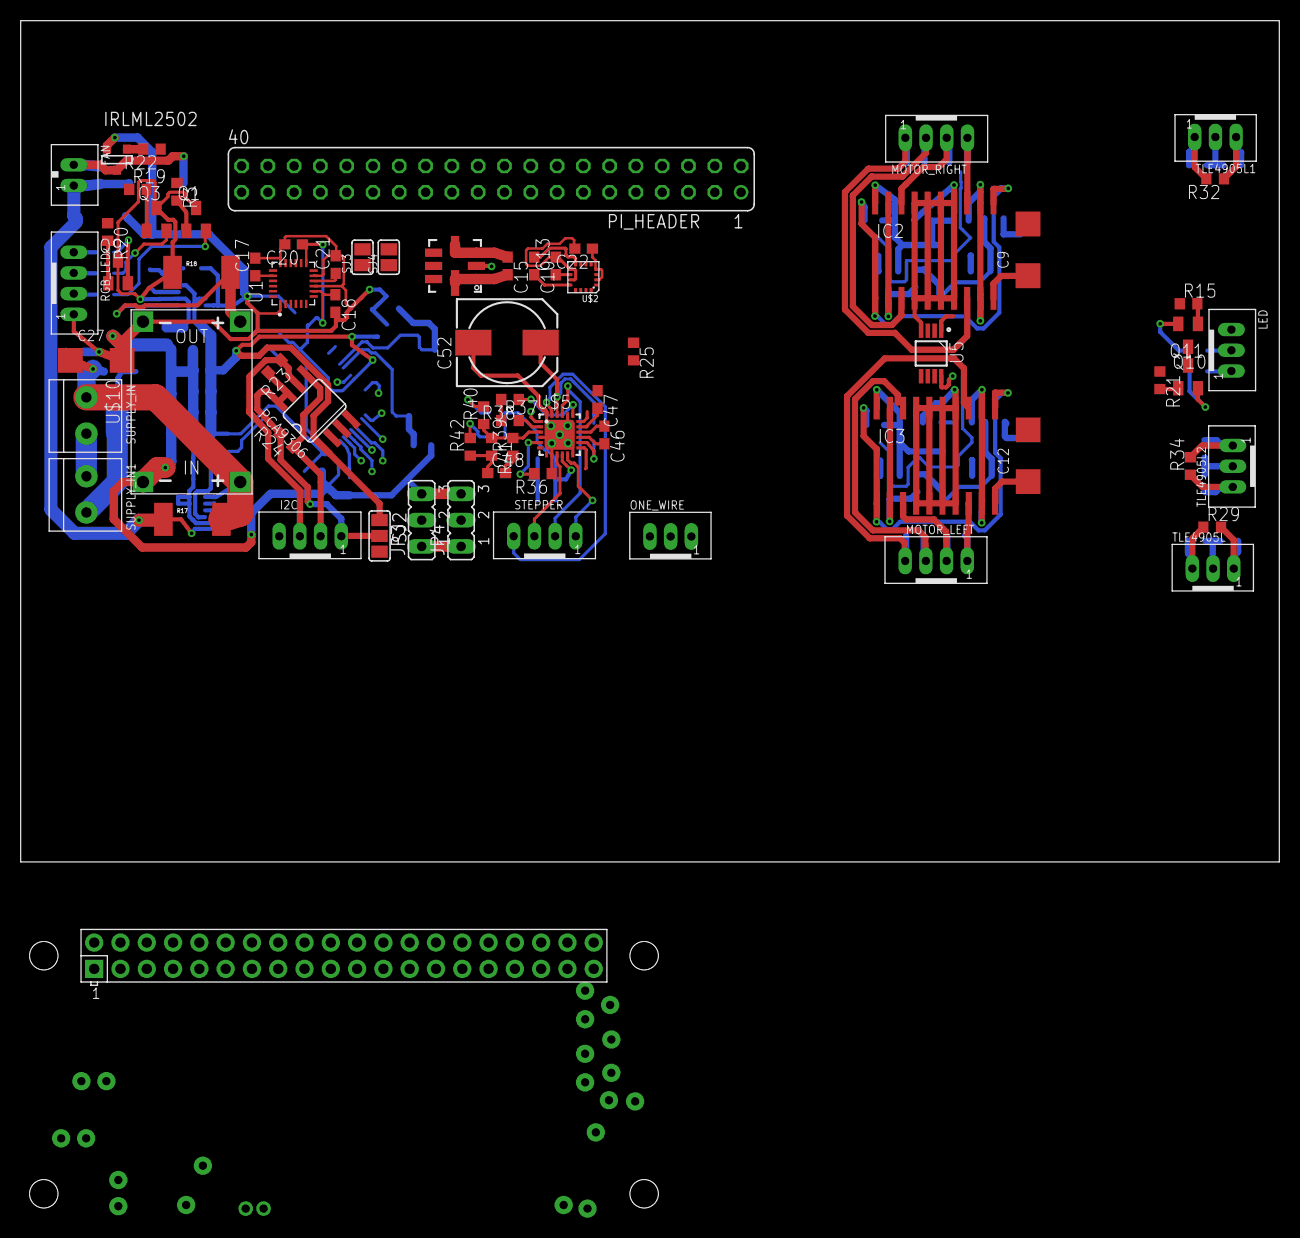
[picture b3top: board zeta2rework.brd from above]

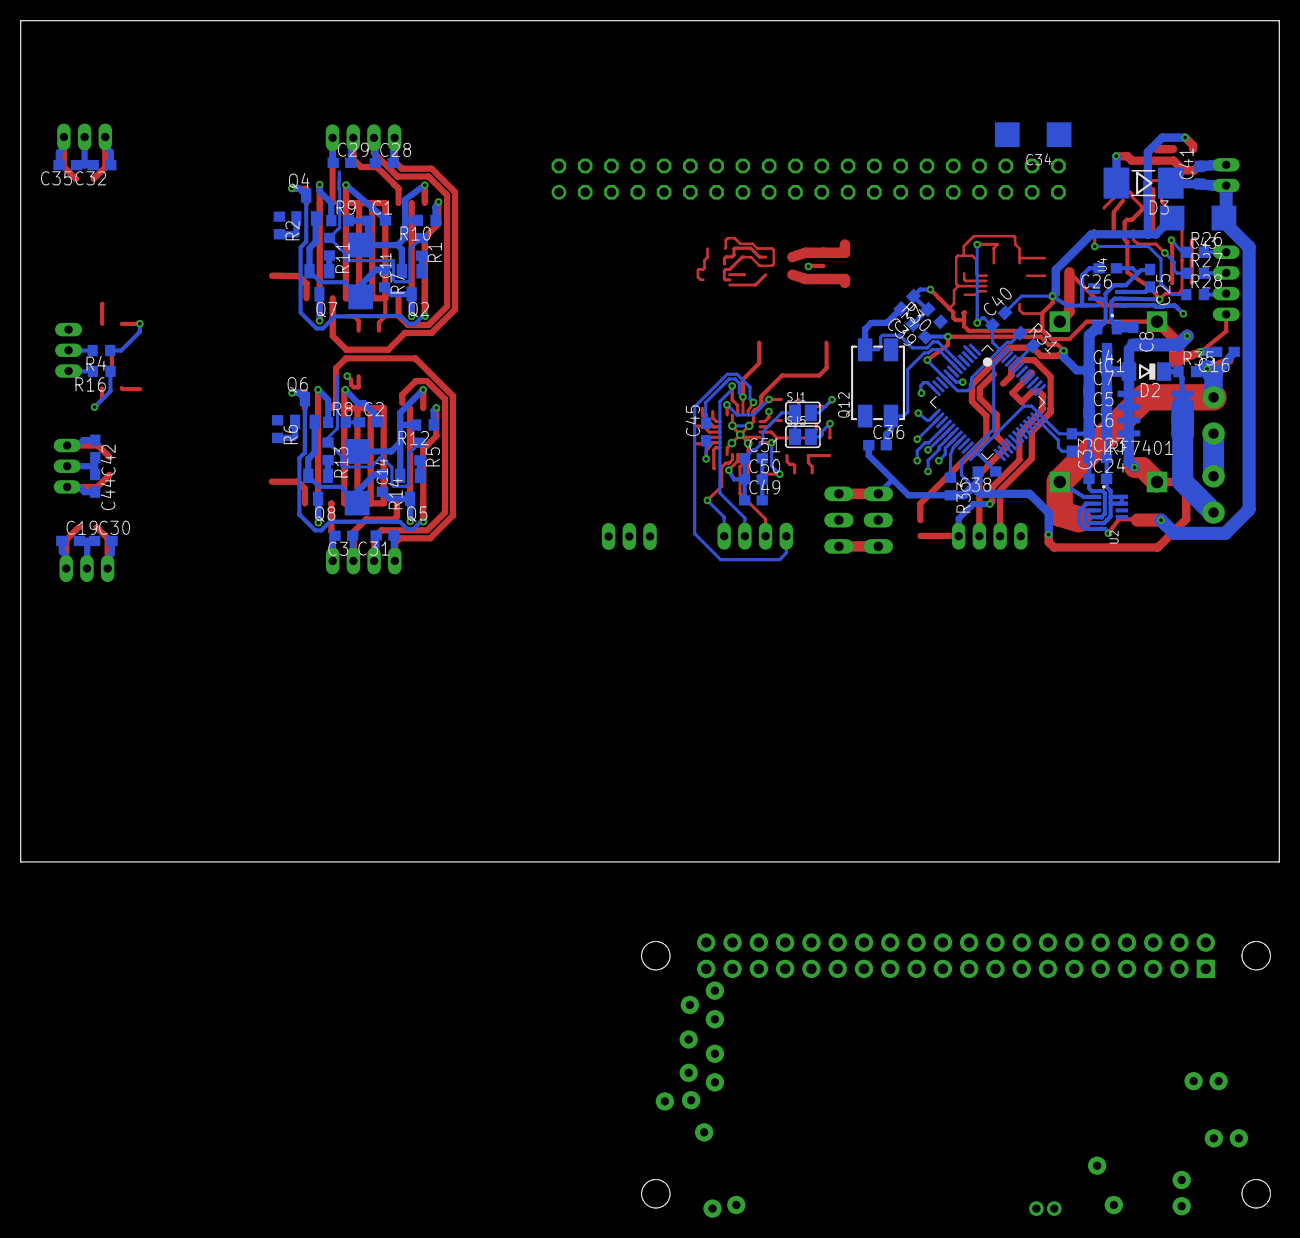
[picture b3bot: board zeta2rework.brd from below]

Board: 2 copper layers, 121.6 x 81.3 mm, 145 parts (74 on the bottom side), 92 nets.

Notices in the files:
parts and their libraries:
crystal-geyer_V1_0: Copyright: Geyer-Electronic
diy-modules: Released under the Creative Commons Attribution 4.0 International License: http://creativecommons.org/licenses/by/4.0
